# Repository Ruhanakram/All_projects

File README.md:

# All_projects
# Second project
# Arduino nano rev3

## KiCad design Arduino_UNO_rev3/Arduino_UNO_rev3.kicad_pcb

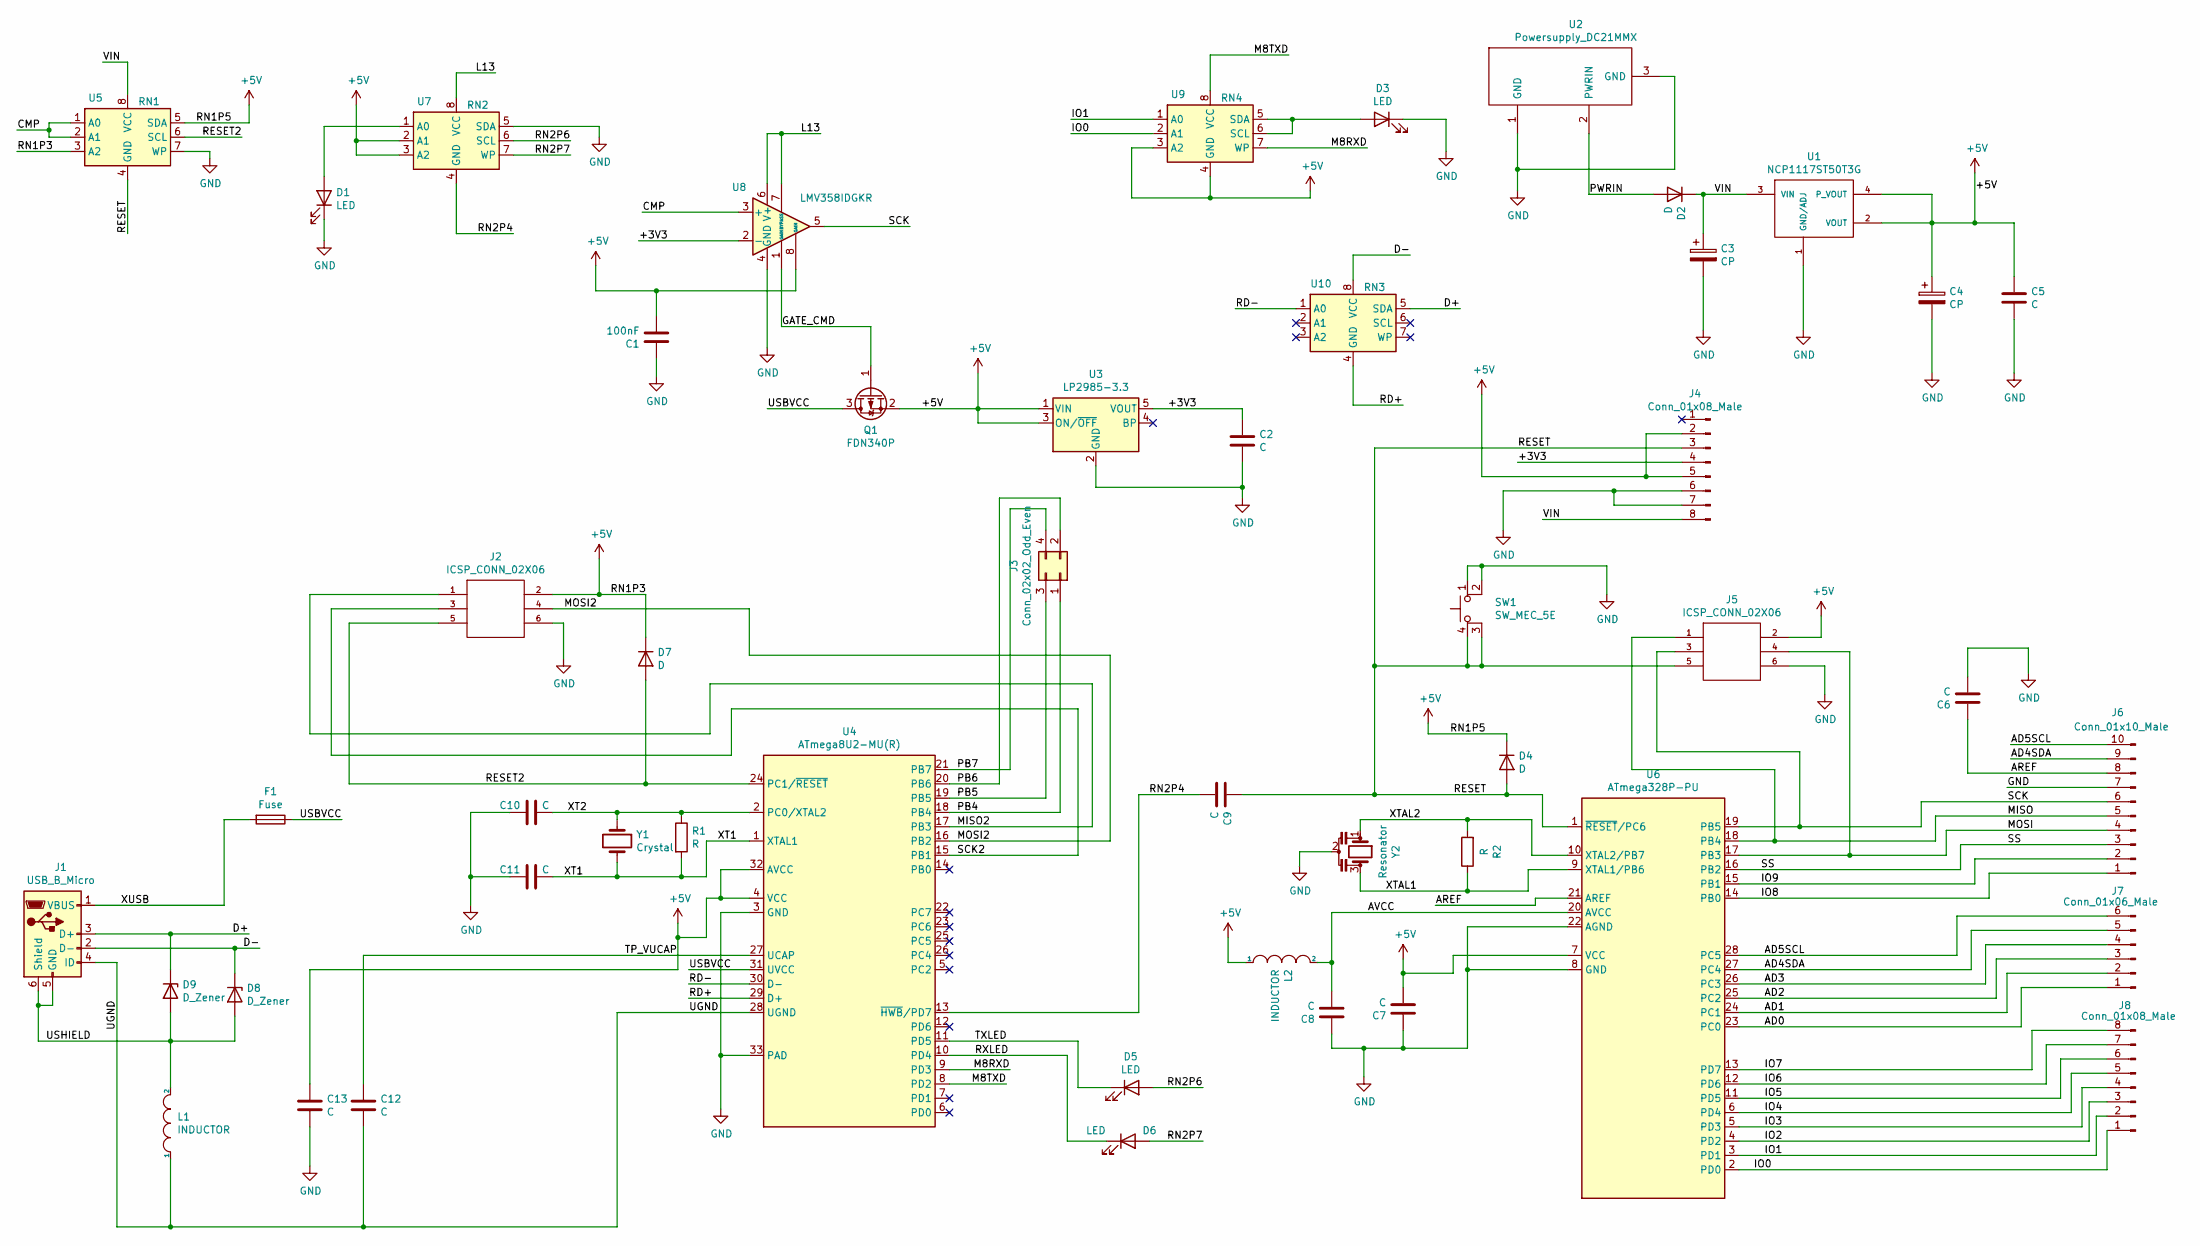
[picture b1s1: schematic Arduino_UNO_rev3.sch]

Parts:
C1: 100nF; C0603-ROUND
C2, C5, C6, C7, C8, C9, C10, C11, C12, C13: C; C0603-ROUND
C3, C4: CP; PANASONIC_D
D1, D5, D6: LED; CHIP-LED0805
D2: D; SMB
D3: LED; LED_0603_1608Metric
D4, D7: D; MINIMELF
D8, D9: D_Zener; CT_CN0603
F1: Fuse; L1812
J1: USB_B_Micro; PN61729
J2, J5: ICSP_CONN_02X06; ICSP_Arduino__connector_UNO
J3: Conn_02x02_Odd_Even; 2X02
J4, J8: Conn_01x08_Male; 1X08
J6: Conn_01x10_Male; 1X10
J7: Conn_01x06_Male; 1X06
L1, L2: INDUCTOR; 0805
Q1: FDN340P; SOT-23
R1, R2: R; R0603-ROUND
SW1: SW_MEC_5E; TS42
U1: NCP1117ST50T3G; SOT223
U2: Powersupply_DC21MMX; POWERSUPPLY_DC-21MM
U3: LP2985-3.3; SOT23-DBV
U4: ATmega8U2-MU(R); QFN-32-1EP_5x5mm_P0.5mm_EP3.1x3.1mm
U5: RN1; CAY16
U6: ATmega328P-PU; DIP-28_W7.62mm
U7: RN2; CAY16
U8: LMV358IDGKR; MSOP08
U9: RN4; CAY16
U10: RN3; CAY16
Y1: Crystal; QS
Y2: Resonator; RESONATOR

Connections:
+5V: C1.1, C4.1, C5.2, C7.1, C13.2, D4.1 (K), D7.1 (K), J2.2, J4.2, J4.5, J5.2, L2.1, Q1.2 (S), U1.2 (VOUT), U1.4 (P_VOUT), U3.1 (VIN), U3.3 (ON/~OFF~), U4.4 (VCC), U4.32 (AVCC), U5.3 (A2), U5.5 (SDA), U6.7 (VCC), U7.2 (A1), U7.3 (A2), U8.8 (GAIN), U9.3 (A2), U9.4 (GND)
/+3V3: C2.2, J4.4, U3.5 (VOUT), U8.2 (-)
/AD0: J7.1, U6.23 (PC0)
/AD1: J7.2, U6.24 (PC1)
/AD2: J7.3, U6.25 (PC2)
/AD3: J7.4, U6.26 (PC3)
/AD4SDA: J6.9, J7.5, U6.27 (PC4)
/AD5SCL: J6.10, J7.6, U6.28 (PC5)
/AREF: C6.2, J6.8, U6.21 (AREF)
/AVCC: C8.1, L2.2, U6.20 (AVCC)
/CMP: U5.1 (A0), U5.2 (A1), U8.3 (+)
/D+: D9.1 (K), J1.3 (D+), U10.5 (SDA)
/D-: D8.1 (K), J1.2 (D-), U10.8 (VCC)
/GATE_CMD: Q1.1 (G), U8.1 (GAIN)
/IO0: J8.1, U6.2 (PD0), U9.2 (A1)
/IO1: J8.2, U6.3 (PD1), U9.1 (A0)
/IO2: J8.3, U6.4 (PD2)
/IO3: J8.4, U6.5 (PD3)
/IO4: J8.5, U6.6 (PD4)
/IO5: J8.6, U6.11 (PD5)
/IO6: J8.7, U6.12 (PD6)
/IO7: J8.8, U6.13 (PD7)
/IO8: J6.1, U6.14 (PB0)
/IO9: J6.2, U6.15 (PB1)
/L13: U7.8 (VCC), U8.6 (V+), U8.7 (BYPASS)
/M8RXD: U4.9 (PD3), U9.7 (WP)
/M8TXD: U4.8 (PD2), U9.8 (VCC)
/MISO: J5.1, J6.5, U6.18 (PB4)
/MISO2: J2.1, U4.17 (PB3)
/MOSI: J5.4, J6.4, U6.17 (PB3)
/MOSI2: J2.4, U4.16 (PB2)
/PB4: J3.1, U4.18 (PB4)
/PB5: J3.3, U4.19 (PB5)
/PB6: J3.2, U4.20 (PB6)
/PB7: J3.4, U4.21 (PB7)
/PWRIN: D2.2 (A), U2.2 (PWRIN)
/RD+: U4.29 (D+), U10.4 (GND)
/RD-: U4.30 (D-), U10.1 (A0)
/RESET: C9.2, D4.2 (A), J4.3, J5.5, SW1.3 (K), SW1.4 (A), U5.4 (GND), U6.1 (~RESET~/PC6)
/RESET2: D7.2 (A), J2.5, U4.24 (PC1/~RESET), U5.6 (SCL)
/RN2P4: C9.1, U4.13 (~HWB~/PD7), U7.4 (GND)
/RN2P6: D5.2 (A), U7.6 (SCL)
/RN2P7: D6.2 (A), U7.7 (WP)
/RXLED: D6.1 (K), U4.10 (PD4)
/SCK: J5.3, J6.6, U6.19 (PB5), U8.5
/SCK2: J2.3, U4.15 (PB1)
/SS: J6.3, U6.16 (PB2)
/TP_VUCAP: C12.2, U4.27 (UCAP)
/TXLED: D5.1 (K), U4.11 (PD5)
/UGND: C12.1, J1.4 (ID), L1.1, U4.28 (UGND)
/USBVCC: F1.1, Q1.3 (D), U4.31 (UVCC)
/USHIELD: D8.2 (A), D9.2 (A), J1.5 (GND), J1.6 (Shield), L1.2
/VIN: C3.1, D2.1 (K), J4.8, U1.3 (VIN), U5.8 (VCC)
/XT1: C11.1, R1.2, U4.1 (XTAL1), Y1.2
/XT2: C10.1, R1.1, U4.2 (PC0/XTAL2), Y1.1
/XTAL1: R2.1, U6.9 (XTAL1/PB6), Y2.3
/XTAL2: R2.2, U6.10 (XTAL2/PB7), Y2.1
/XUSB: F1.2, J1.1 (VBUS)
GND: C1.2, C2.1, C3.2, C4.2, C5.1, C6.1, C7.2, C8.2, C10.2, C11.2, C13.1, D1.1 (K), D3.1 (K), J2.6, J4.6, J4.7, J5.6, J6.7, SW1.1, SW1.2, U1.1 (GND/ADJ), U2.1 (GND), U2.3 (GND), U3.2 (GND), U4.3 (GND), U4.33 (GND), U5.7 (WP), U6.8 (GND), U6.22 (AGND), U7.5 (SDA), U8.4 (GND), Y2.2
unnamed: D1.2 (A), U7.1 (A0)
unnamed: D3.2 (A), U9.5 (SDA), U9.6 (SCL)

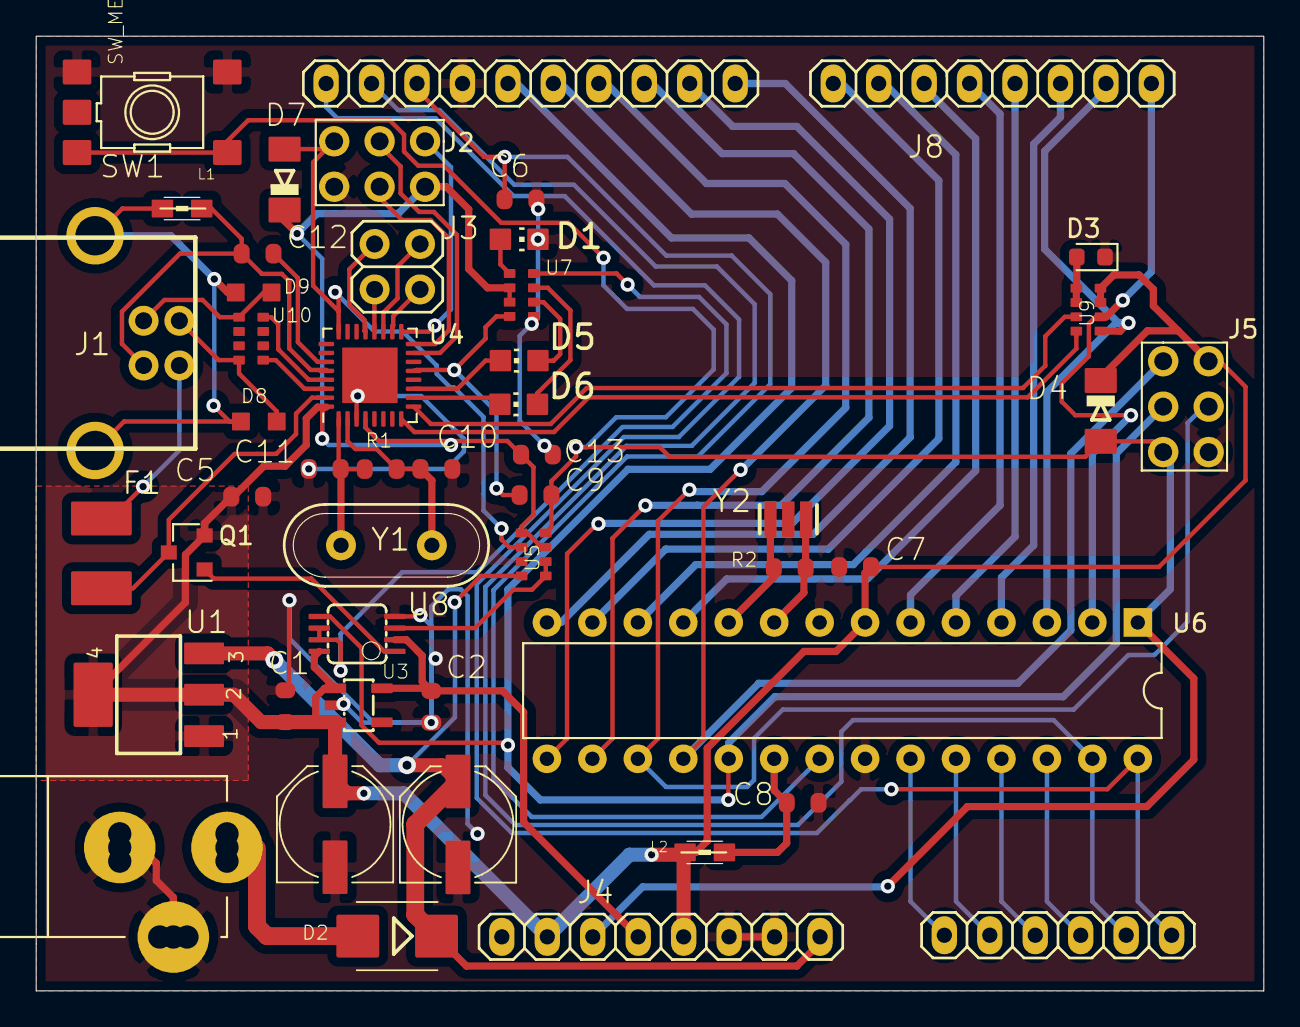
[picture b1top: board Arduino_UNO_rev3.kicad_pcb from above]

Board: 2 copper layers, 68.6 x 53.4 mm, 49 parts (0 on the bottom side), 61 nets.

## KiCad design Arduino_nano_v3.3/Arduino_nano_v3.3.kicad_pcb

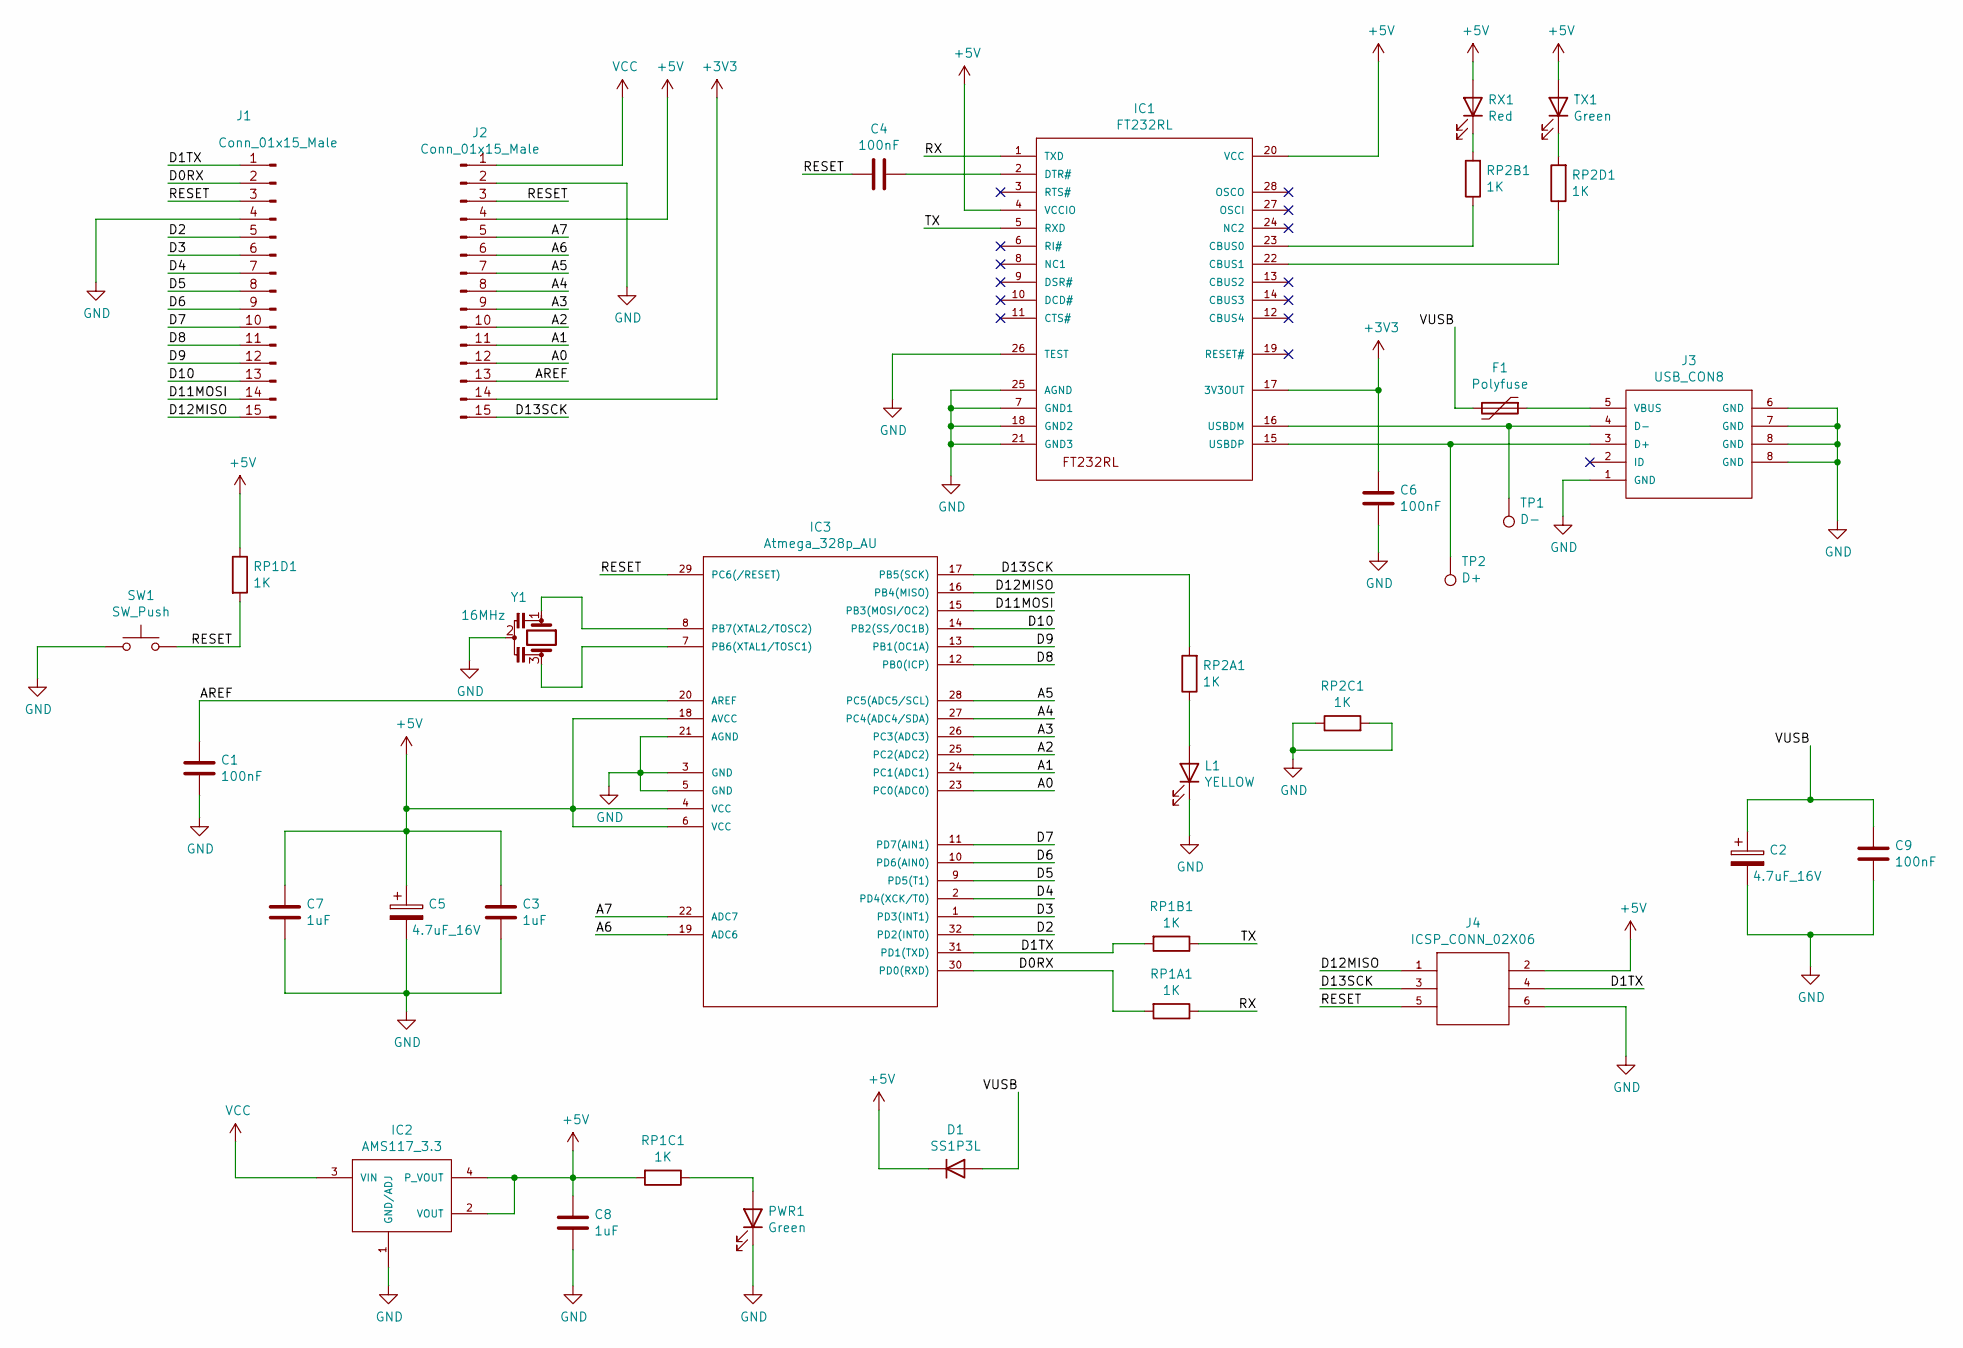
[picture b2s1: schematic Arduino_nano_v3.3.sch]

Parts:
C1, C4, C6, C9: 100nF; C_0603_1608Metric
C2, C5: 4.7uF_16V; C_1206_3216Metric
C3, C7, C8: 1uF; C_0603_1608Metric
D1: SS1P3L; SS1P3L_diode
F1: Polyfuse; Fuse_0603_1608Metric
IC1: FT232RL; SSOP-28_5.3x10.2mm_P0.65mm
IC2: AMS117_3.3; SOT-23
IC3: Atmega_328p_AU; TQFP-32_7x7mm_P0.8mm
J1, J2: Conn_01x15_Male; PinHeader_1x15_P2.54mm_Vertical
J3: USB_CON8; Micro_usb_connector_4_THT_pads
J4: ICSP_CONN_02X06; ICSP_Arduino__connector
L1: YELLOW; LED_0603_1608Metric
PWR1: Green; LED_0603_1608Metric
RP1A1, RP1B1, RP1C1, RP1D1, RP2A1, RP2B1, RP2C1, RP2D1: 1K; R_0603_1608Metric
RX1: Red; LED_0603_1608Metric
SW1: SW_Push; SW_SPST_B3U-1000P
TP1: D-; TestPoint_Pad_1.0x1.0mm
TP2: D+; TestPoint_Pad_1.0x1.0mm
TX1: Green; LED_0603_1608Metric
Y1: 16MHz; OSC_CSTCE16M0V53-R0

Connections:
+3V3: C6.1, IC1.17 (3V3OUT), J2.14
+5V: C3.1, C5.1, C7.1, C8.1, D1.1 (K), IC1.4 (VCCIO), IC1.20 (VCC), IC2.2 (VOUT), IC2.4 (P_VOUT), IC3.4 (VCC), IC3.6 (VCC), IC3.18 (AVCC), J2.4, J4.2, RP1C1.2, RP1D1.1, RX1.2 (A), TX1.2 (A)
/A0: IC3.23 (PC0(ADC0)), J2.12
/A1: IC3.24 (PC1(ADC1)), J2.11
/A2: IC3.25 (PC2(ADC2)), J2.10
/A3: IC3.26 (PC3(ADC3)), J2.9
/A4: IC3.27 (PC4(ADC4/SDA)), J2.8
/A5: IC3.28 (PC5(ADC5/SCL)), J2.7
/A6: IC3.19 (ADC6), J2.6
/A7: IC3.22 (ADC7), J2.5
/AREF: C1.1, IC3.20 (AREF), J2.13
/D0RX: IC3.30 (PD0(RXD)), J1.2, RP1A1.2
/D1TX: IC3.31 (PD1(TXD)), J1.1, J4.4, RP1B1.2
/D2: IC3.32 (PD2(INT0)), J1.5
/D3: IC3.1 (PD3(INT1)), J1.6
/D4: IC3.2 (PD4(XCK/T0)), J1.7
/D5: IC3.9 (PD5(T1)), J1.8
/D6: IC3.10 (PD6(AIN0)), J1.9
/D7: IC3.11 (PD7(AIN1)), J1.10
/D8: IC3.12 (PB0(ICP)), J1.11
/D9: IC3.13 (PB1(OC1A)), J1.12
/D10: IC3.14 (PB2(SS/OC1B)), J1.13
/D11MOSI: IC3.15 (PB3(MOSI/OC2)), J1.14
/D12MISO: IC3.16 (PB4(MISO)), J1.15, J4.1
/D13SCK: IC3.17 (PB5(SCK)), J2.15, J4.3, RP2A1.2
/RESET: C4.1, IC3.29 (PC6(/RESET)), J1.3, J2.3, J4.5, RP1D1.2, SW1.2
/RX: IC1.1 (TXD), RP1A1.1
/TX: IC1.5 (RXD), RP1B1.1
/VUSB: C2.1, C9.1, D1.2 (A), F1.2
GND: C1.2, C2.2, C3.2, C5.2, C6.2, C7.2, C8.2, C9.2, IC1.7 (GND1), IC1.18 (GND2), IC1.21 (GND3), IC1.25 (AGND), IC1.26 (TEST), IC2.1 (GND/ADJ), IC3.3 (GND), IC3.5 (GND), IC3.21 (AGND), J1.4, J2.2, J3.1 (GND), J3.6 (GND), J3.7 (GND), J3.8 (GND), J4.6, L1.1 (K), PWR1.1 (K), RP2C1.1, RP2C1.2, SW1.1, Y1.2
unnamed: C4.2, IC1.2 (DTR#)
unnamed: F1.1, J3.5 (VBUS)
unnamed: IC1.15 (USBDP), J3.3 (D+), TP2.1
unnamed: IC1.16 (USBDM), J3.4 (D-), TP1.1
unnamed: IC1.22 (CBUS1), RP2D1.1
unnamed: IC1.23 (CBUS0), RP2B1.1
unnamed: IC3.7 (PB6(XTAL1/TOSC1)), Y1.3
unnamed: IC3.8 (PB7(XTAL2/TOSC2)), Y1.1
unnamed: L1.2 (A), RP2A1.1
unnamed: PWR1.2 (A), RP1C1.1
unnamed: RP2B1.2, RX1.1 (K)
unnamed: RP2D1.2, TX1.1 (K)
VCC: IC2.3 (VIN), J2.1

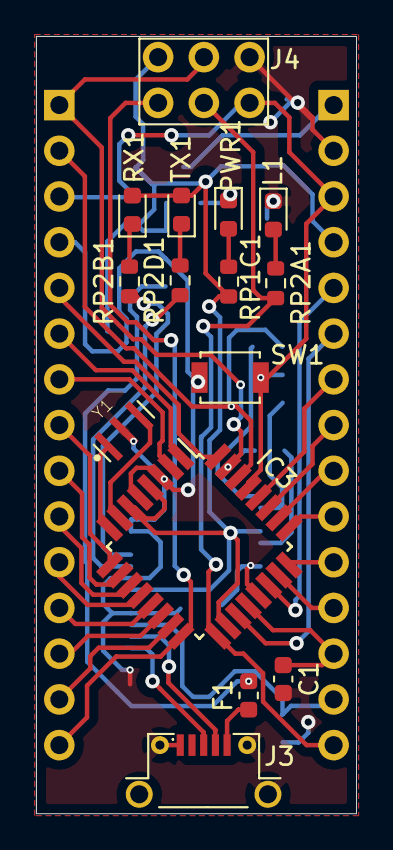
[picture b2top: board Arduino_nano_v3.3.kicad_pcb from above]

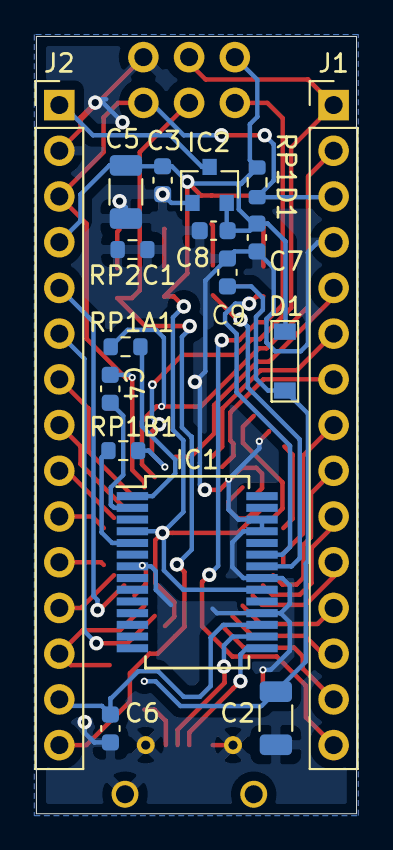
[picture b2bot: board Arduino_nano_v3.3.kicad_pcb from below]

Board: 2 copper layers, 17.8 x 43.2 mm, 32 parts (17 on the bottom side), 43 nets.

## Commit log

2021-04-26 README.md
2021-04-26 Arduino nano Rev 3.3 project first commit
2021-04-26 Changes in Shematics
2021-04-26 Changes in Schematics
2021-04-30 Updated layout design
2021-05-02 Layout design
2021-05-12 Adding arduino UNO project
2021-05-12 Adding some extra symbls
2021-05-12 Adding footprints and layout
2021-05-13 Updated schematics and footprint layout
2021-05-13 Copplete routings and layout desig
2021-05-13 Complete layout desig and routings
